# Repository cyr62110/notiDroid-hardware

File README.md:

notiDroid-hardware
==================

Hardware part of the notiDroid project

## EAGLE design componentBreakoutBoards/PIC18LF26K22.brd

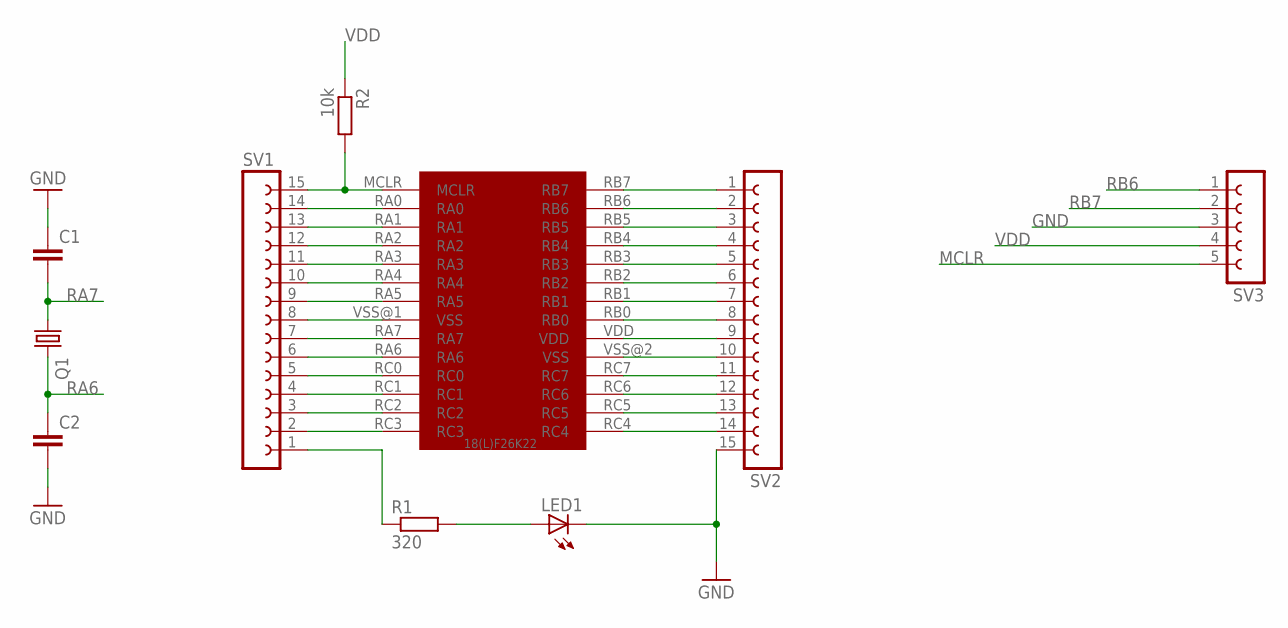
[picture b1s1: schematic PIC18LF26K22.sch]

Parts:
C1, C2: C-EU025-024X044; C025-024X044
LED1: LED5MM
Q1: CRYSTALHC49S; HC49/S
R1: 320; 0207/10
R2: 10k; 0207/10
SV1, SV2: FE15-1; FE15
SV3: FE05-1
U$1: PIC18(L)F26K22; 28-LEAD_SOIC

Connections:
GND: C1.1, C2.2, LED1.K (C), SV1.8, SV2.10, SV2.15, SV3.3, U$1.VSS@1 (VSS), U$1.VSS@2 (VSS)
MCLR: R2.2, SV1.15, SV3.5, U$1.MCLR
unnamed: R1.1, SV1.1
unnamed: SV1.14, U$1.RA0
unnamed: SV1.13, U$1.RA1
unnamed: SV1.12, U$1.RA2
unnamed: SV1.11, U$1.RA3
unnamed: SV1.10, U$1.RA4
unnamed: SV1.9, U$1.RA5
unnamed: LED1.A, R1.2
unnamed: SV1.5, U$1.RC0
unnamed: SV1.4, U$1.RC1
unnamed: SV1.3, U$1.RC2
unnamed: SV1.2, U$1.RC3
unnamed: SV2.3, U$1.RB5
unnamed: SV2.4, U$1.RB4
unnamed: SV2.5, U$1.RB3
unnamed: SV2.6, U$1.RB2
unnamed: SV2.7, U$1.RB1
unnamed: SV2.8, U$1.RB0
unnamed: SV2.11, U$1.RC7
unnamed: SV2.12, U$1.RC6
unnamed: SV2.13, U$1.RC5
unnamed: SV2.14, U$1.RC4
RA6: C2.1, Q1.2, SV1.6, U$1.RA6
RA7: C1.2, Q1.1, SV1.7, U$1.RA7
RB6: SV2.2, SV3.1, U$1.RB6
RB7: SV2.1, SV3.2, U$1.RB7
VDD: R2.1, SV2.9, SV3.4, U$1.VDD

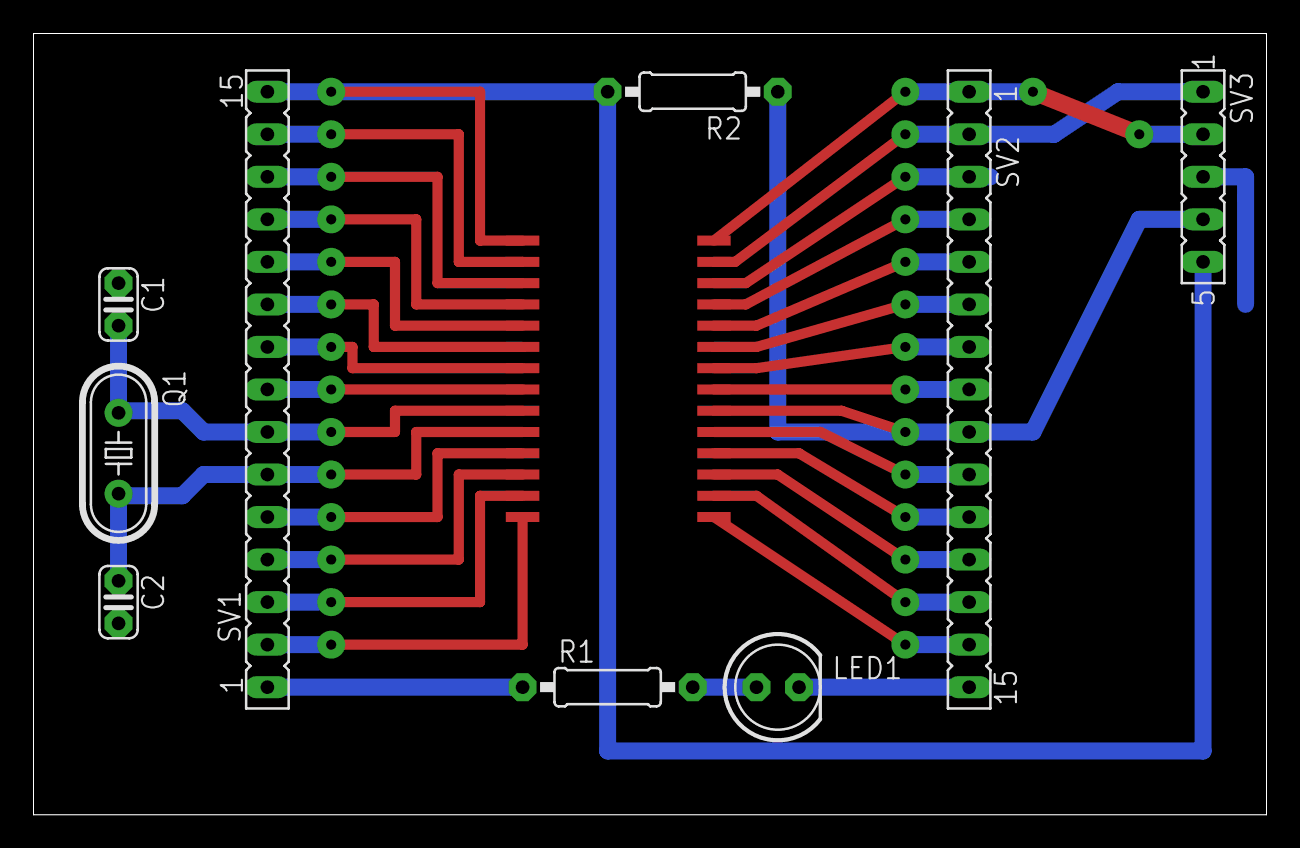
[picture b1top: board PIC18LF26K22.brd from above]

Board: 2 copper layers, 73.6 x 46.7 mm, 10 parts (0 on the bottom side), 29 nets.

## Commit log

2014-03-10 PCB for BLE112 chip.
2014-03-24 Added more components
2014-03-24 WIP : first dev board
